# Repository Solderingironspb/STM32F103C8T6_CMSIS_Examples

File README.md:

# STM32F103C8T6_CMSIS_Examples
Примеры проектов на CMSIS

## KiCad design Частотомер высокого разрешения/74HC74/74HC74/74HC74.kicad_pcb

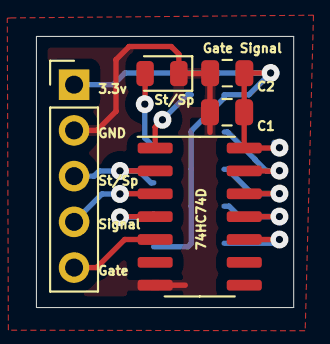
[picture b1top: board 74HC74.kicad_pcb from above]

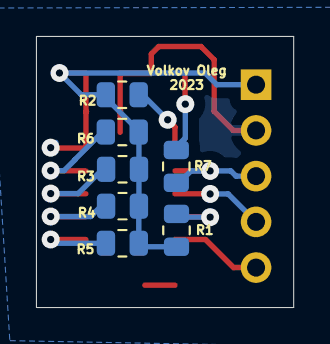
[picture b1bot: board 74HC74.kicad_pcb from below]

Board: 2 copper layers, 14.3 x 15.1 mm, 12 parts (7 on the bottom side), 12 nets.

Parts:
74HC74D: 74HC74; SOIC-14_3.9x8.7mm_P1.27mm
C1: 0.1u; C_0805_2012Metric
C2: 10u; C_0805_2012Metric
J1: conn; PinHeader_1x05_P2.54mm_Vertical
R1, R2, R3, R4, R5, R6: 10k; R_0805_2012Metric
R7: 1.2k; R_0805_2012Metric
St/Sp: LED; LED_0805_2012Metric

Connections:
+3V3: 74HC74D.14, C1.1, C2.1, J1.1, R1.1, R2.2, R3.1, R4.1, R5.1, R6.1
GND: 74HC74D.7, C1.2, C2.2, J1.2, St/Sp.1
Gate: 74HC74D.5, J1.5
unnamed: R7.1, St/Sp.2
unnamed: 74HC74D.4, R1.2
unnamed: 74HC74D.1, R2.1
unnamed: 74HC74D.12, R3.2
unnamed: 74HC74D.11, R4.2
unnamed: 74HC74D.10, R5.2
unnamed: 74HC74D.13, R6.2
Signal: 74HC74D.3, J1.4
Start-Stop: 74HC74D.2, J1.3, R7.2

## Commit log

2023-03-21 2-канальный частотомер. 1 канал - 36 МГц. 2 канала - 18 МГц
2023-05-28 Частотомер высокого разрешения
